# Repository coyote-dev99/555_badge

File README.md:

# 555 Badge
Id card badge schematics and pcb design in KiCAD

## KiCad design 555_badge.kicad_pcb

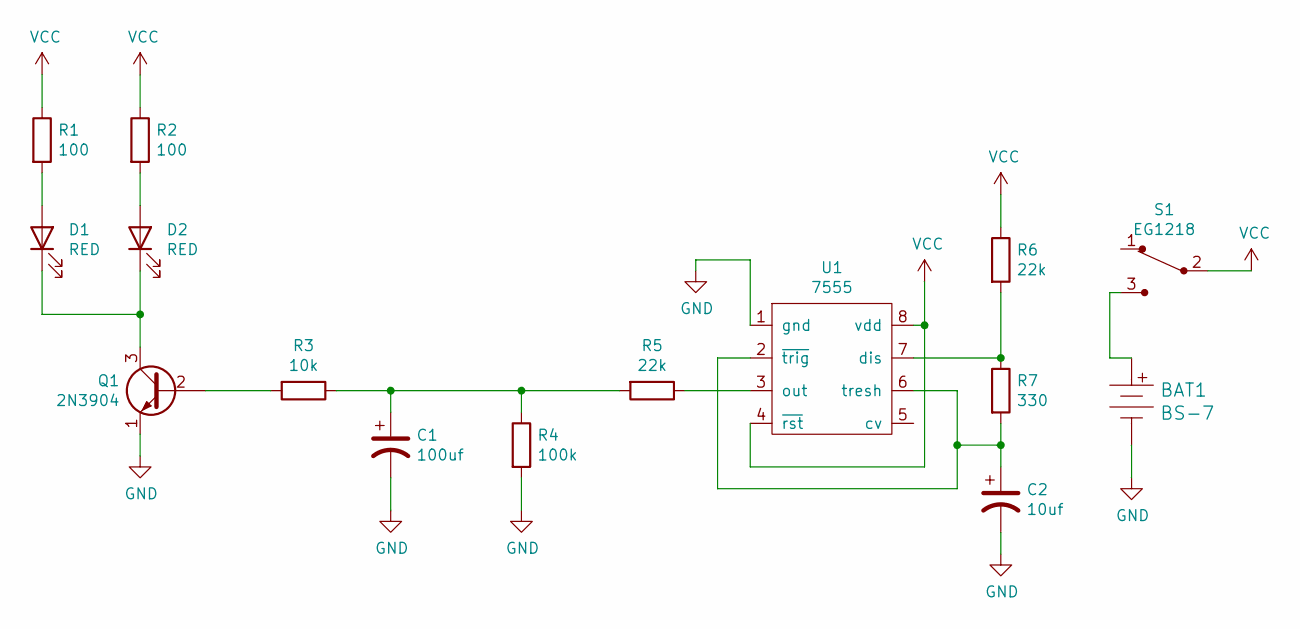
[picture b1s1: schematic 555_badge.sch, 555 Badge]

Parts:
BAT1: BS-7; Battery_Holder_Coin_2032_BS-7; MPN BS-7; Digi-Key_PN BS-7-ND
C1: 100uf; CP_Radial_D6.3mm_P2.50mm
C2: 10uf; CP_Radial_D5.0mm_P2.00mm
D1, D2: RED; LED_D3.0mm
Q1: 2N3904; TO-92-3_Formed_Leads
R1, R2: 100; R_Axial_DIN0207_L6.3mm_D2.5mm_P7.62mm_Horizontal
R3: 10k; R_Axial_DIN0207_L6.3mm_D2.5mm_P7.62mm_Horizontal
R4: 100k; R_Axial_DIN0207_L6.3mm_D2.5mm_P7.62mm_Horizontal
R5, R6: 22k; R_Axial_DIN0207_L6.3mm_D2.5mm_P7.62mm_Horizontal
R7: 330; R_Axial_DIN0207_L6.3mm_D2.5mm_P7.62mm_Horizontal
S1: EG1218; Switch_Slide_11.6x4mm_EG1218; MPN EG1218; Digi-Key_PN EG1903-ND
U1: 7555; IC755-PDIP

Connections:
GND: BAT1.Neg, C1.2, C2.2, Q1.1 (E), R4.2, U1.1 (gnd)
unnamed: BAT1.Pos, S1.3
unnamed: C1.1, R3.1, R4.1, R5.2
unnamed: C2.1, R7.2, U1.2 (~trig), U1.6 (tresh)
unnamed: D1.1 (K), D2.1 (K), Q1.3 (C)
unnamed: D1.2 (A), R1.2
unnamed: D2.2 (A), R2.2
unnamed: Q1.2 (B), R3.2
unnamed: R5.1, U1.3 (out)
unnamed: R6.2, R7.1, U1.7 (dis)
VCC: R1.1, R2.1, R6.1, S1.2, U1.4 (~rst), U1.8 (vdd)

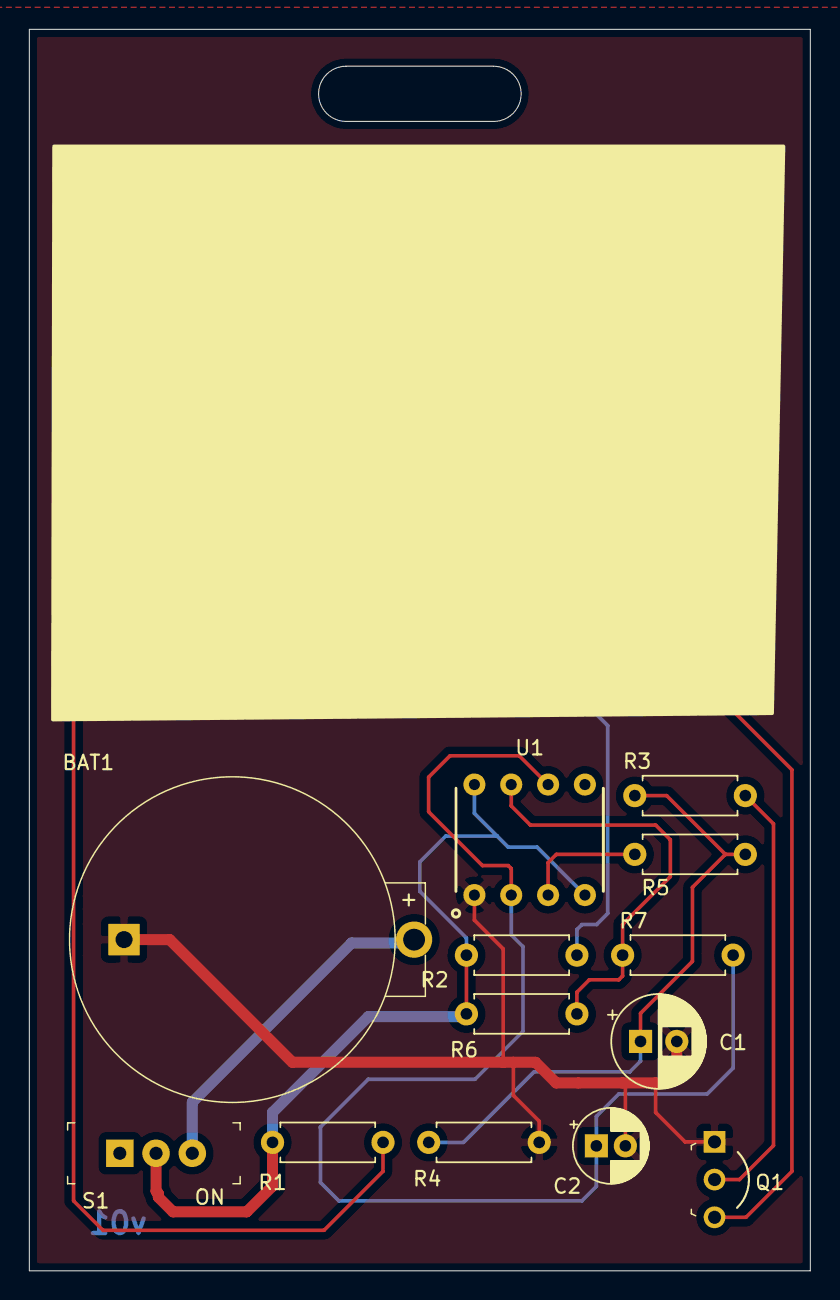
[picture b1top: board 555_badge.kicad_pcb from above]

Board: 2 copper layers, 53.8 x 85.6 mm, 15 parts (0 on the bottom side), 11 nets.

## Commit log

2021-11-13 Add readme file
2021-11-13 Add project files

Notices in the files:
555_badge.kicad_pcb:
License: CC BY 4.0
555_badge.sch:
creativecommons.org/license/by/4.0
